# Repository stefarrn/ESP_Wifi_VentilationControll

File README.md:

# ESP_Wifi_VentilationControll
UPDATE:
after assembling the first prototype and making it work, I have applied all necessary changes to the designs and V2.0 should work straight away

modification Board in order to controll older ventilation systems over Wifi.

required tools:
1. soldering iron and solder
2. hotplate. heatgun or reflow oven for soldering the surface mount components
3. solder paste and tweezers for soldering surface mount components (ordering a stencil together with the PCBs is highly recommended)
5. computer with USB cable and USB to FTDI adapter or frog pin programmer for the ESP8266
6. Phone or tablet cabaple of running the Arduino IoT remote app
7. some prototyping cables for programming
8. multimeter or oscilocope for troubleshooting

HOW TO USE:
1. order all required parts aswell as the PCB
2. assemble the PCB acording to the schematic (make sure the buck converter is set to around 4-5 Volts before powerup)
3. flash the ESP8266 module over the Pinheader with the help of a USB to FTDI adapter (if you flashed your module before installing it this step can be skipped)
4. solder all the buttons onto pads A1 to D2, where 1 corresponds to the positive and 2 to the negative of the button
5. solder powersupply cables to the VCC and GND pads on the PCB
6. download the Arduino IoT remote app onto your device and log in with the account your ESP is connecting to (this can be done with multiple devices such that everyone can use the ventilation controller)
7. once all this is done and working you can leanback and enjoy :)

OPTIONAL:
1. if your ventilation system uses an LED to indicate wheter it is turned on or off, the pin of said LED that changes potential relative to ground can be soldered ont the LED1 pad for feedback (you might need to change the values for on and off in the software)
2. you can of course also modify the code and UI to your needs

Credits:
ESP8266 schematic symbol, footprint and 3d model by J.Dunmire 
(though I slightly modified the silkscreen on the footprint as iw was overlapping the pads)
buck converter schematic symbol, and footprint were done by me, 3d model by Wilfredo B. de los Reyes I (downloaded from grabcad.com)
schematic and PCB design by me

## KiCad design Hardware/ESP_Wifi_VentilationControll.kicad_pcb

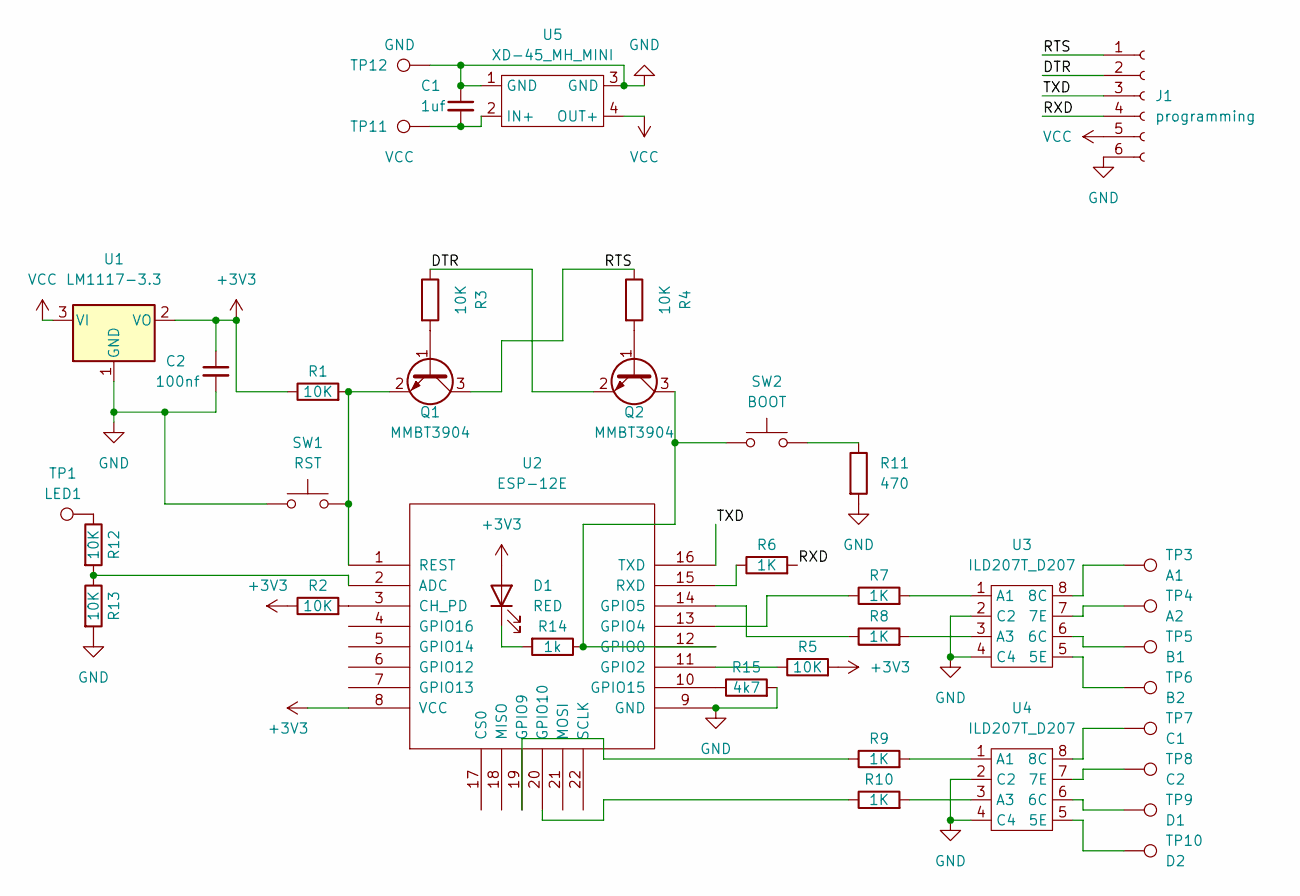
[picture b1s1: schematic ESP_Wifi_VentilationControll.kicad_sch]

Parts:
C1: 1uf; C_0805_2012Metric
C2: 100nf; C_0805_2012Metric
D1: RED; LED_1206_3216Metric
J1: programming; PinHeader_1x06_P2.54mm_Vertical
Q1, Q2: MMBT3904; SOT-23
R1, R2, R3, R4, R5, R12, R13: 10K; R_1206_3216Metric
R6, R7, R8, R9, R10: 1K; R_1206_3216Metric
R11: 470; R_1206_3216Metric
R14: 1k; R_1206_3216Metric
R15: 4k7; R_1206_3216Metric
SW1: RST; SW_SPST_TL3342
SW2: BOOT; SW_SPST_TL3342
TP1: LED1; SolderWirePad_1x01_SMD_1x2mm
TP3: A1; SolderWirePad_1x01_SMD_1x2mm
TP4: A2; SolderWirePad_1x01_SMD_1x2mm
TP5: B1; SolderWirePad_1x01_SMD_1x2mm
TP6: B2; SolderWirePad_1x01_SMD_1x2mm
TP7: C1; SolderWirePad_1x01_SMD_1x2mm
TP8: C2; SolderWirePad_1x01_SMD_1x2mm
TP9: D1; SolderWirePad_1x01_SMD_1x2mm
TP10: D2; SolderWirePad_1x01_SMD_1x2mm
TP11: VCC; SolderWirePad_1x01_SMD_1x2mm
TP12: GND; SolderWirePad_1x01_SMD_1x2mm
U1: LM1117-3.3; SOT-223-3_TabPin2
U2: ESP-12E; ESP-12E_SMD
U3, U4: ILD207T_D207; SOIC-8W_5.3x5.3mm_P1.27mm
U5: XD-45_MH_MINI; XD-45 MH mini

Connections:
+3V3: C2.1, D1.2 (A), R1.1, R2.1, R5.2, U1.2 (VO), U2.8 (VCC)
/DTR: J1.2, Q2.2 (E), R3.1
/RTS: J1.1, Q1.3 (C), R4.1
/RXD: J1.4, R6.2
/TXD: J1.3, U2.16 (TXD)
GND: C1.1, C2.2, J1.6, R11.2, R13.2, R15.2, SW1.1, TP12.1, U1.1 (GND), U2.9 (GND), U3.2 (C2), U3.4 (C4), U4.2 (C2), U4.4 (C4), U5.1 (GND), U5.3 (GND)
unnamed: C1.2, TP11.1, U5.2 (IN+)
unnamed: D1.1 (K), R14.2
unnamed: Q1.1 (B), R3.2
unnamed: Q1.2 (E), R1.2, SW1.2, U2.1 (REST)
unnamed: Q2.1 (B), R4.2
unnamed: Q2.3 (C), R14.1, SW2.1, U2.12 (GPIO0)
unnamed: R2.2, U2.3 (CH_PD)
unnamed: R5.1, U2.11 (GPIO2)
unnamed: R6.1, U2.15 (RXD)
unnamed: R7.1, U2.13 (GPIO4)
unnamed: R7.2, U3.1 (A1)
unnamed: R8.1, U2.14 (GPIO5)
unnamed: R8.2, U3.3 (A3)
unnamed: R9.1, U2.19 (GPIO9)
unnamed: R9.2, U4.1 (A1)
unnamed: R10.1, U2.20 (GPIO10)
unnamed: R10.2, U4.3 (A3)
unnamed: R11.1, SW2.2
unnamed: R12.1, TP1.1
unnamed: R12.2, R13.1, U2.2 (ADC)
unnamed: R15.1, U2.10 (GPIO15)
unnamed: TP3.1, U3.8 (8C)
unnamed: TP4.1, U3.7 (7E)
unnamed: TP5.1, U3.6 (6C)
unnamed: TP6.1, U3.5 (5E)
unnamed: TP7.1, U4.8 (8C)
unnamed: TP8.1, U4.7 (7E)
unnamed: TP9.1, U4.6 (6C)
unnamed: TP10.1, U4.5 (5E)
VCC: J1.5, U1.3 (VI), U5.4 (OUT+)

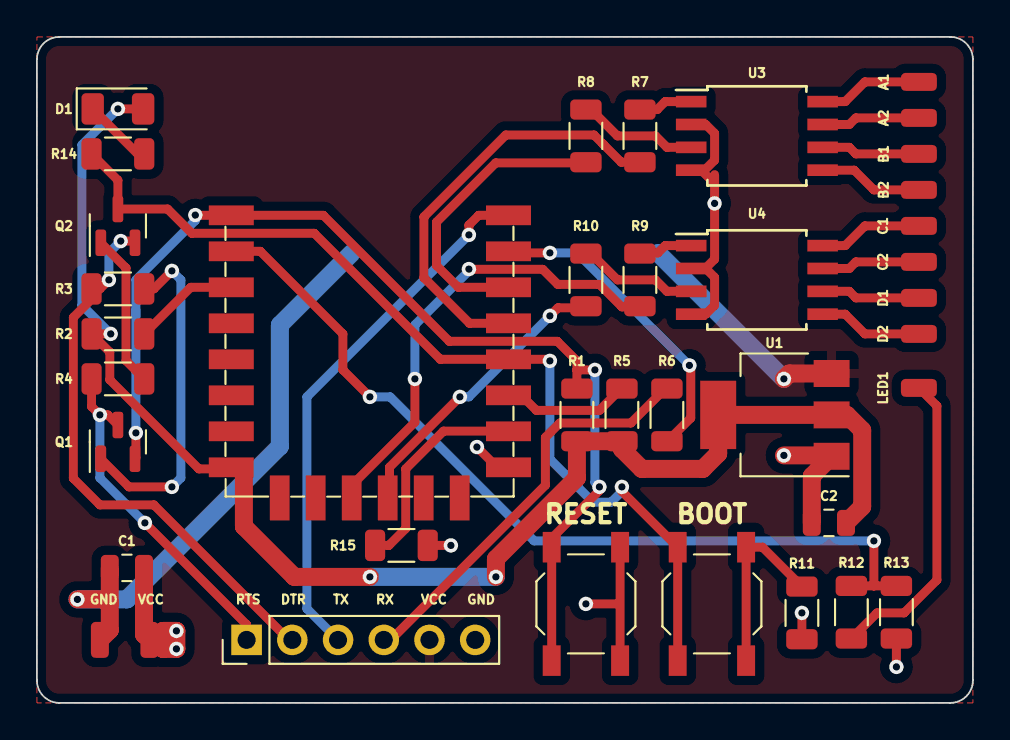
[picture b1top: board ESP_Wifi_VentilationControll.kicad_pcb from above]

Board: 2 copper layers, 52.0 x 37.0 mm, 39 parts (1 on the bottom side), 36 nets.

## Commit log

2022-05-11 created schematic and PCB
2022-05-11 changed filenames
2022-05-11 ESP_Wifi_VentilationControll
2022-05-11 added smoothing capacitors
2022-05-11 added pictures folder
2022-05-11 Create LICENSE
2022-05-11 added status LED
2022-05-13 added librarys
2022-05-13 idk why these chages even exist lol
2022-05-16 idk why it didn't push this last time xD
2022-05-17 generated gerber files
2022-05-20 rendered new pictures
2022-06-04 added pictures
2022-06-09 added missing resistor values
2022-06-14 fixed some footprints and added missing resistor
2022-06-14 removed old gerber files
2022-06-15 added actual image
2023-08-17 final touches
